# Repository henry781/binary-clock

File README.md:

# Binary Clock

A wall clock that shows the time in pure binary on 17 LEDs. It keeps time
with a 32.768 kHz watch crystal, sets itself from the DCF77 radio time
signal and dims its LEDs with the light of the room. Through-hole parts
(the DCF77 receiver module aside), on a round 180 mm board that is the
face of the clock.

> **Disclaimer:** this is a personal study project, shared as is in the
> hope that it is useful. It comes with no warranty and no support; build
> and use it at your own risk.

## Features

- **Display**: 17 LEDs, 10 mm: 5 red for the hours, 6 green for the
  minutes, 6 blue for the seconds. The time is held by three CD4040
  counters and shown through three 74HC245 buffers, with no multiplexing.
- **Timekeeping**: ATmega328P, Timer2 in asynchronous mode on a
  32.768 kHz crystal, CPU on its internal 8 MHz oscillator.
- **DCF77 synchronization**: a noise-tolerant software decoder that
  integrates the time over several minutes and follows DST changes and
  leap seconds. It never loaded a wrong time in 6,000 hours of simulated
  noisy signals; the rare corner cases are described in the
  [decoder documentation](docs/dcf77-decoder.md#validation).
- **Automatic dimming**: TEPT5700 light sensor, 488 Hz PWM in 2048 steps,
  from 0.1 % in the dark to full brightness in daylight.
- **Setting by hand**: three buttons, hours +1, minutes +1, seconds to 0.
- **Power**: 5 V from a cable coming out of the wall, on a screw terminal,
  with reverse-polarity protection; about 25 mA in a lit room.
- **Tested**: the decoder runs in a PC simulator against synthetic noise
  and a noise model fitted to recordings of the real receiver; CI builds
  the firmware and runs the regression suite.

Hardware revision B has been built and tested with this firmware.

## Reading the clock

Each row is a binary number, with weights increasing from left to right
as printed on the board. For 14:37:05:

```
             1  2  4  8  16 32
HOURS        ○  ●  ●  ●  ○          2 + 4 + 8  = 14
MINUTES      ●  ○  ●  ○  ○  ●       1 + 4 + 32 = 37
SECONDS      ●  ○  ●  ○  ○  ○       1 + 4      =  5
```

## How it works

```mermaid
flowchart LR
    XTAL["32.768 kHz crystal"] --> MCU["ATmega328P"]
    DCF["DCF77 receiver"] --> MCU
    LDR["Light sensor"] --> MCU
    BTN["3 buttons"] --> MCU
    MCU -- "clock and reset pulses" --> CNT["3 × CD4040 counters"]
    CNT --> BUF["3 × 74HC245 buffers"]
    MCU -- "dimming PWM on output enable" --> BUF
    BUF --> LED["17 LEDs"]
```

Every second, Timer2 wakes the microcontroller, which sends a clock pulse
to the seconds counter and carries into the minutes and hours counters.
The counter outputs drive the LEDs through the buffers; the
microcontroller dims them all at once by switching the buffers' output
enable at 488 Hz with a duty cycle that follows the room light. When a
DCF77 time is confirmed, the firmware reloads the counters and re-aligns
the phase of its seconds on the top of the minute.

## The board

| 3D render, front | PCB layout (front and back copper) |
|:---:|:---:|
|  |  |

Rendered from the KiCad project with `kicad-cli pcb render` and
`kicad-cli pcb export svg`. The 3D model shows every LED in red; on the
real clock the minutes are green and the seconds blue.

## Repository layout

| Path | Content |
|------|---------|
| [`hardware/`](hardware) | KiCad 10 project (schematic, PCB, project libraries) and bill of materials |
| [`firmware/binary_clock/`](firmware/binary_clock) | clock firmware, an Arduino sketch for MiniCore |
| [`firmware/test/`](firmware/test) | PC simulator and regression tests of the DCF77 decoder |
| [`firmware/tools/`](firmware/tools) | bring-up sketches and a crystal drift logger |
| [`docs/`](docs) | documentation |

## Documentation

- [Hardware](docs/hardware.md): circuit description, pinout, PCB.
- [Firmware](docs/firmware.md): building, programming, build options, architecture, debug output.
- [DCF77 decoder](docs/dcf77-decoder.md): how the time is recovered from a noisy signal, and how well.
- [Building the clock](docs/assembly.md): ordering the PCB, assembly, bring-up, mounting, troubleshooting.

## Quick start

1. Order the PCB ([ordering](docs/assembly.md#ordering-the-pcb)) and the
   parts listed in [`hardware/bom.csv`](hardware/bom.csv).
2. Assemble and check the board step by step: [assembly.md](docs/assembly.md).
3. Program the ATmega328P through the ISP header with an Arduino Uno as
   programmer: [firmware.md](docs/firmware.md#building-and-programming).
   With avr-gcc and avrdude:

   ```sh
   make -C firmware
   make -C firmware fuses flash PORT=/dev/ttyACM0
   ```

4. Run the decoder tests on a PC:

   ```sh
   make -C firmware/test test
   ```

## License

[MIT](LICENSE), hardware and software. `firmware/tools/arduino_isp_clock` is
derived from the ArduinoISP example, © 2008–2011 Randall Bohn, BSD license
(see the notice in the file).

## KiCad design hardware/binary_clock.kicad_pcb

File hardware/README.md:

# Hardware

KiCad 10 project of the clock, board revision B.

| File | Content |
|------|---------|
| `binary_clock.kicad_pro` | project file, open this one |
| `binary_clock.kicad_sch` | schematic |
| `binary_clock.kicad_pcb` | PCB |
| `binary_clock.kicad_sym`, `binary_clock.pretty/` | project libraries: symbol and footprint of the DCF77 module |
| `sym-lib-table`, `fp-lib-table` | project library tables |
| [`bom.csv`](bom.csv) | bill of materials |

Round board, Ø 180 mm, two layers. All parts go on the front; they are
through-hole parts, except the DCF77 module. The circuit is described in
[docs/hardware.md](../docs/hardware.md); fabrication files and assembly
are covered in [docs/assembly.md](../docs/assembly.md).

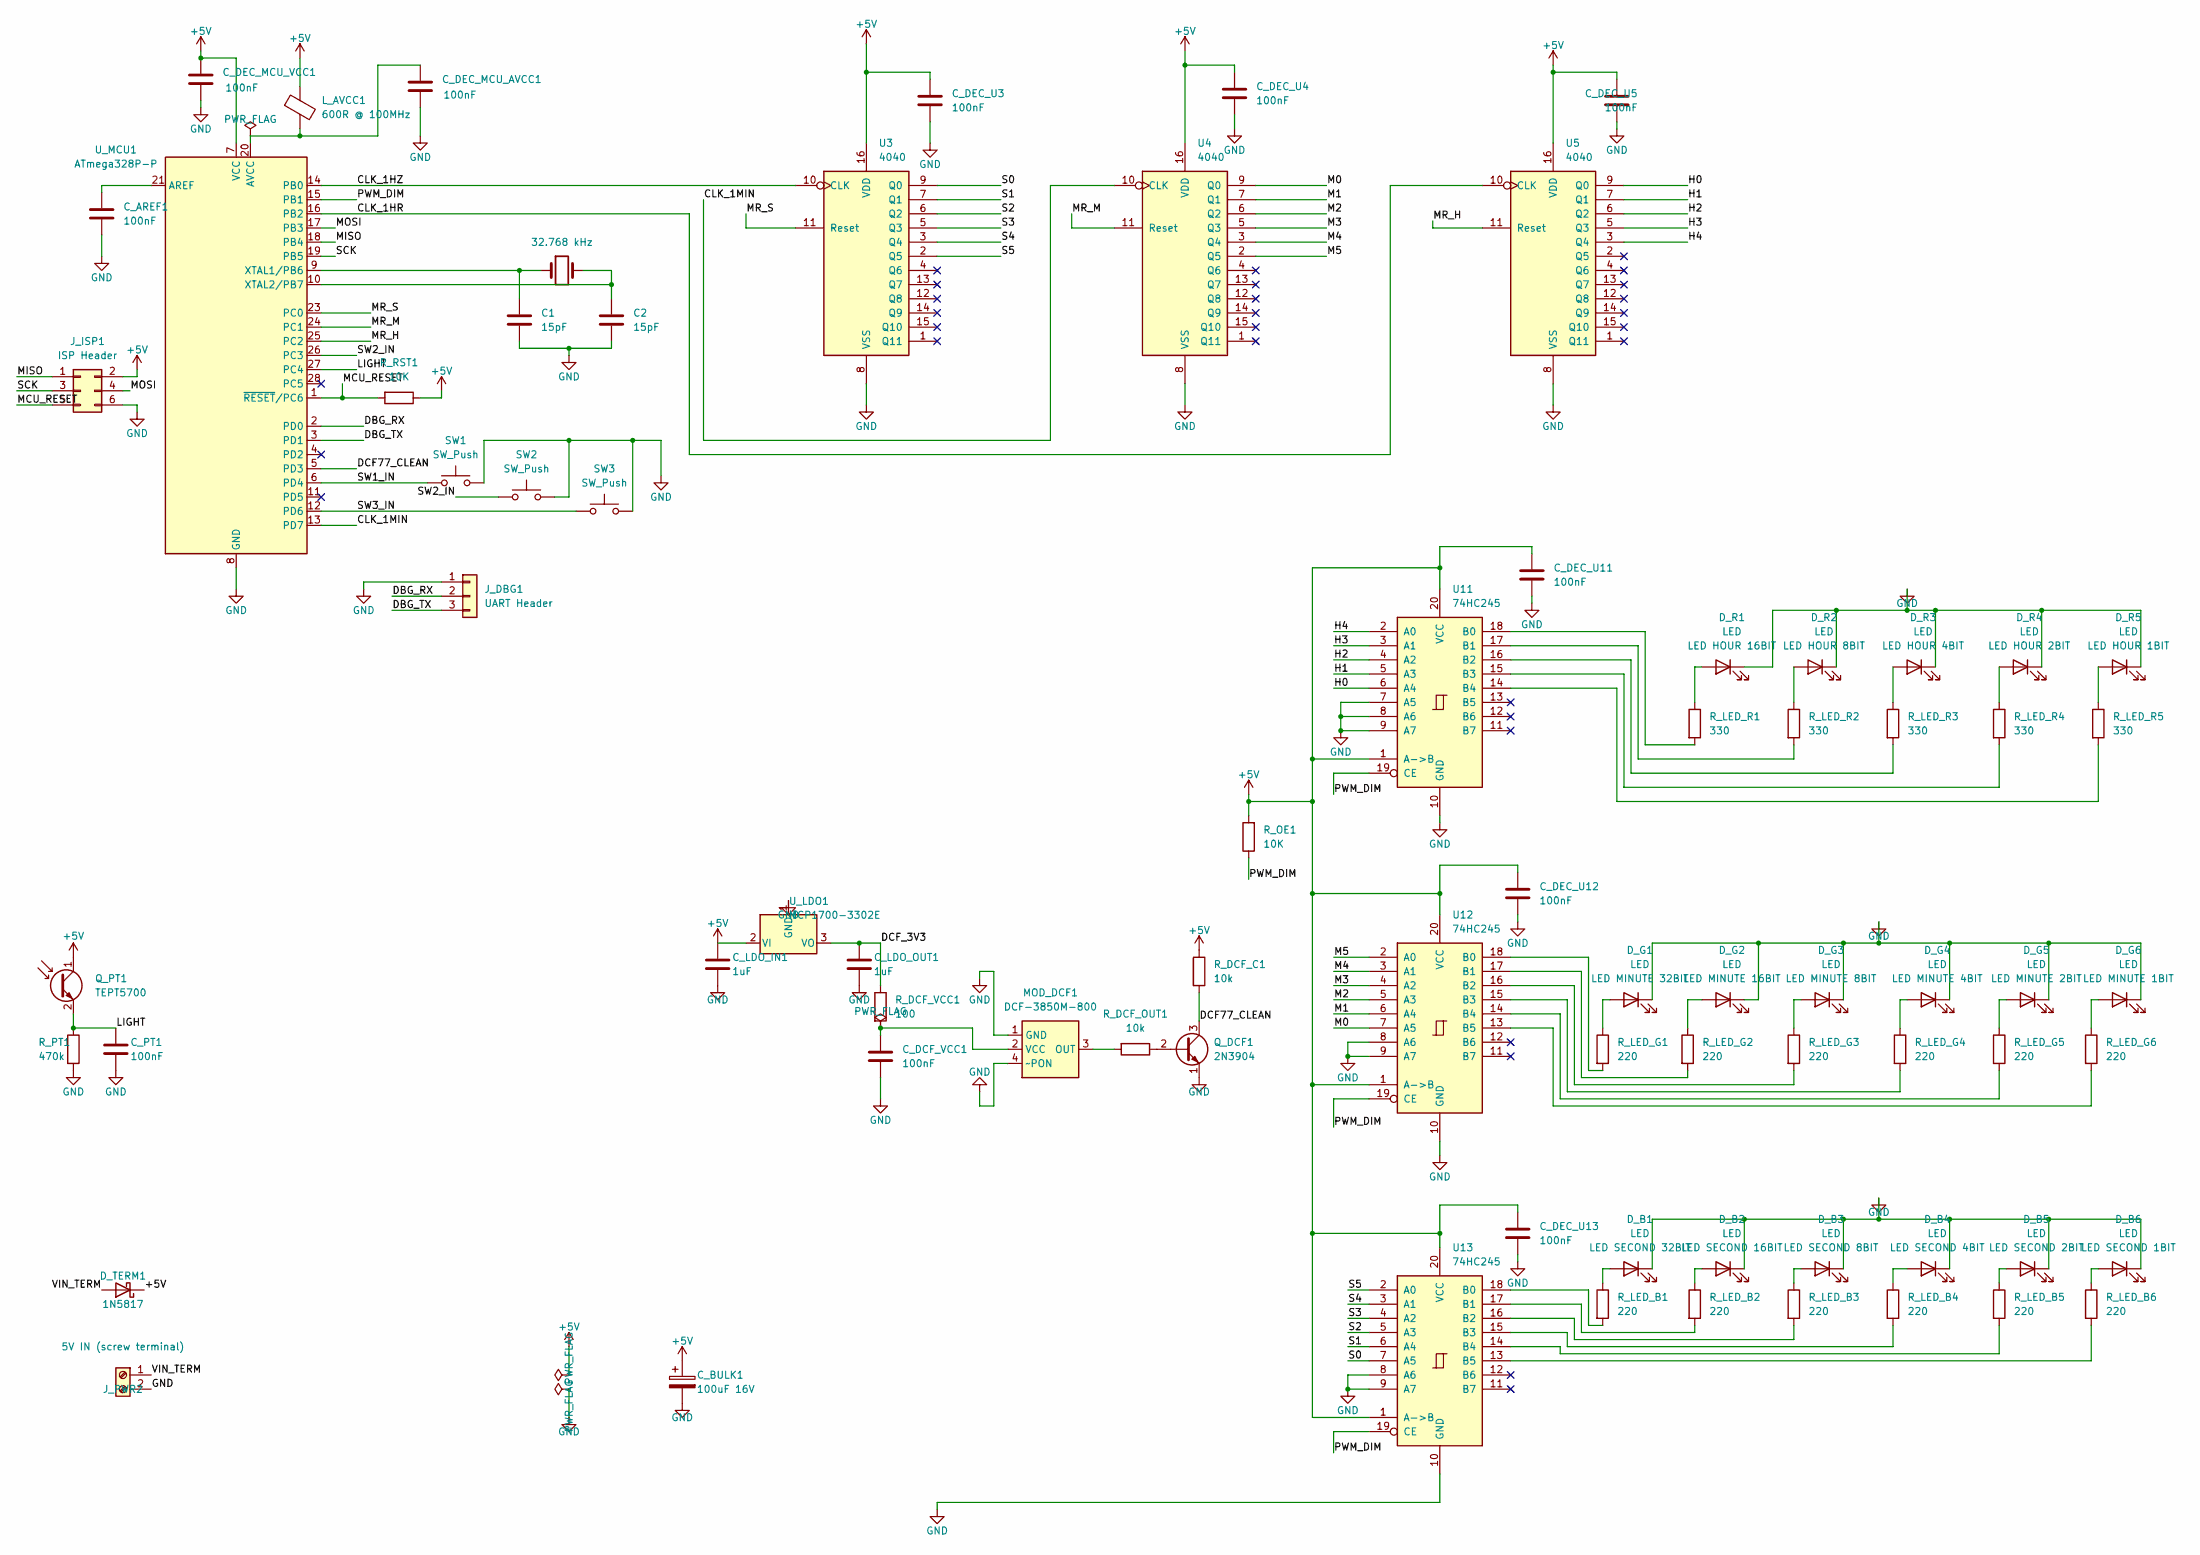
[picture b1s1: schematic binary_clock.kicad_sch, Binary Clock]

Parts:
C1, C2: 15pF; C_Disc_D5.0mm_W2.5mm_P5.00mm
C_AREF1: 100nF; C_Disc_D5.0mm_W2.5mm_P5.00mm
C_BULK1: 100uF 16V; CP_Radial_D6.3mm_P2.50mm
C_DCF_VCC1: 100nF; C_Disc_D5.0mm_W2.5mm_P5.00mm
C_DEC_MCU_AVCC1: 100nF; C_Disc_D5.0mm_W2.5mm_P5.00mm
C_DEC_MCU_VCC1: 100nF; C_Disc_D5.0mm_W2.5mm_P5.00mm
C_DEC_U3, C_DEC_U4, C_DEC_U5, C_DEC_U11, C_DEC_U12, C_DEC_U13: 100nF; C_Disc_D5.0mm_W2.5mm_P5.00mm
C_LDO_IN1: 1uF; C_Disc_D5.0mm_W2.5mm_P5.00mm
C_LDO_OUT1: 1uF; C_Disc_D5.0mm_W2.5mm_P5.00mm
C_PT1: 100nF; C_Disc_D5.0mm_W2.5mm_P5.00mm
D_B1, D_B2, D_B3, D_B4, D_B5, D_B6: LED; LED_D10.0mm
D_G1, D_G2, D_G3, D_G4, D_G5, D_G6: LED; LED_D10.0mm
D_R1, D_R2, D_R3, D_R4, D_R5: LED; LED_D10.0mm
D_TERM1: 1N5817; D_DO-41_SOD81_P10.16mm_Horizontal
J_DBG1: UART Header; PinHeader_1x03_P2.54mm_Vertical
J_ISP1: ISP Header; PinHeader_2x03_P2.54mm_Vertical
J_PWR2: 5V IN (screw terminal); TerminalBlock_Phoenix_MKDS-1,5-2_1x02_P5.00mm_Horizontal
L_AVCC1: 600R @ 100MHz; L_Axial_L9.5mm_D4.0mm_P12.70mm_Horizontal_Fastron_SMCC
MOD_DCF1: DCF-3850M-800; DCF77_Module_RC8000_Castellated_21.5x13mm
Q_DCF1: 2N3904; TO-92_Inline_Wide
Q_PT1: TEPT5700; LED_D5.0mm
R_DCF_C1: 10k; R_Axial_DIN0207_L6.3mm_D2.5mm_P10.16mm_Horizontal
R_DCF_OUT1: 10k; R_Axial_DIN0207_L6.3mm_D2.5mm_P10.16mm_Horizontal
R_DCF_VCC1: 100; R_Axial_DIN0207_L6.3mm_D2.5mm_P10.16mm_Horizontal
R_LED_B1, R_LED_B2, R_LED_B3, R_LED_B4, R_LED_B5, R_LED_B6: 220; R_Axial_DIN0207_L6.3mm_D2.5mm_P10.16mm_Horizontal
R_LED_G1, R_LED_G2, R_LED_G3, R_LED_G4, R_LED_G5, R_LED_G6: 220; R_Axial_DIN0207_L6.3mm_D2.5mm_P10.16mm_Horizontal
R_LED_R1, R_LED_R2, R_LED_R3, R_LED_R4, R_LED_R5: 330; R_Axial_DIN0207_L6.3mm_D2.5mm_P10.16mm_Horizontal
R_OE1: 10K; R_Axial_DIN0207_L6.3mm_D2.5mm_P10.16mm_Horizontal
R_PT1: 470k; R_Axial_DIN0207_L6.3mm_D2.5mm_P10.16mm_Horizontal
R_RST1: 10K; R_Axial_DIN0207_L6.3mm_D2.5mm_P10.16mm_Horizontal
SW1, SW2, SW3: SW_Push; SW_PUSH_6mm
U3, U4, U5: 4040; DIP-16_W7.62mm
U11, U12, U13: 74HC245; DIP-20_W7.62mm
U_LDO1: MCP1700-3302E; TO-92_Inline_Wide
U_MCU1: ATmega328P-P; DIP-28_W7.62mm
Y1: 32.768 kHz; Crystal_C38-LF_D3.0mm_L8.0mm_Horizontal

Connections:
+5V: C_BULK1.1, C_DEC_MCU_VCC1.1, C_DEC_U3.1, C_DEC_U4.1, C_DEC_U5.1, C_DEC_U11.1, C_DEC_U12.1, C_DEC_U13.1, C_LDO_IN1.1, D_TERM1.1 (K), J_ISP1.2, L_AVCC1.1, Q_PT1.1 (C), R_DCF_C1.1, R_OE1.2, R_RST1.1, U3.16 (VDD), U4.16 (VDD), U5.16 (VDD), U11.1 (A->B), U11.20 (VCC), U12.1 (A->B), U12.20 (VCC), U13.1 (A->B), U13.20 (VCC), U_LDO1.2 (VI), U_MCU1.7 (VCC)
/CLK_1HR: U5.10 (CLK), U_MCU1.16 (PB2)
/CLK_1HZ: U3.10 (CLK), U_MCU1.14 (PB0)
/CLK_1MIN: U4.10 (CLK), U_MCU1.13 (PD7)
/DBG_RX: J_DBG1.2, U_MCU1.2 (PD0)
/DBG_TX: J_DBG1.3, U_MCU1.3 (PD1)
/DCF77_CLEAN: Q_DCF1.3 (C), R_DCF_C1.2, U_MCU1.5 (PD3)
/DCF_3V3: C_LDO_OUT1.1, R_DCF_VCC1.1, U_LDO1.3 (VO)
/H0: U5.9 (Q0), U11.6 (A4)
/H1: U5.7 (Q1), U11.5 (A3)
/H2: U5.6 (Q2), U11.4 (A2)
/H3: U5.5 (Q3), U11.3 (A1)
/H4: U5.3 (Q4), U11.2 (A0)
/LIGHT: C_PT1.1, Q_PT1.2 (E), R_PT1.1, U_MCU1.27 (PC4)
/M0: U4.9 (Q0), U12.7 (A5)
/M1: U4.7 (Q1), U12.6 (A4)
/M2: U4.6 (Q2), U12.5 (A3)
/M3: U4.5 (Q3), U12.4 (A2)
/M4: U4.3 (Q4), U12.3 (A1)
/M5: U4.2 (Q5), U12.2 (A0)
/MCU_RESET: J_ISP1.5, R_RST1.2, U_MCU1.1 (~RESET/PC6)
/MISO: J_ISP1.1, U_MCU1.18 (PB4)
/MOSI: J_ISP1.4, U_MCU1.17 (PB3)
/MR_H: U5.11 (Reset), U_MCU1.25 (PC2)
/MR_M: U4.11 (Reset), U_MCU1.24 (PC1)
/MR_S: U3.11 (Reset), U_MCU1.23 (PC0)
/PWM_DIM: R_OE1.1, U11.19 (CE), U12.19 (CE), U13.19 (CE), U_MCU1.15 (PB1)
/S0: U3.9 (Q0), U13.7 (A5)
/S1: U3.7 (Q1), U13.6 (A4)
/S2: U3.6 (Q2), U13.5 (A3)
/S3: U3.5 (Q3), U13.4 (A2)
/S4: U3.3 (Q4), U13.3 (A1)
/S5: U3.2 (Q5), U13.2 (A0)
/SCK: J_ISP1.3, U_MCU1.19 (PB5)
/SW1_IN: SW1.1, U_MCU1.6 (PD4)
/SW2_IN: SW2.1, U_MCU1.26 (PC3)
/SW3_IN: SW3.1, U_MCU1.12 (PD6)
/VIN_TERM: D_TERM1.2 (A), J_PWR2.1
GND: C1.2, C2.2, C_AREF1.2, C_BULK1.2, C_DCF_VCC1.2, C_DEC_MCU_AVCC1.2, C_DEC_MCU_VCC1.2, C_DEC_U3.2, C_DEC_U4.2, C_DEC_U5.2, C_DEC_U11.2, C_DEC_U12.2, C_DEC_U13.2, C_LDO_IN1.2, C_LDO_OUT1.2, C_PT1.2, D_B1.1 (K), D_B2.1 (K), D_B3.1 (K), D_B4.1 (K), D_B5.1 (K), D_B6.1 (K), D_G1.1 (K), D_G2.1 (K), D_G3.1 (K), D_G4.1 (K), D_G5.1 (K), D_G6.1 (K), D_R1.1 (K), D_R2.1 (K), D_R3.1 (K), D_R4.1 (K), D_R5.1 (K), J_DBG1.1, J_ISP1.6, J_PWR2.2, MOD_DCF1.1 (GND), MOD_DCF1.4 (~PON), Q_DCF1.1 (E), R_PT1.2, SW1.2, SW2.2, SW3.2, U3.8 (VSS), U4.8 (VSS), U5.8 (VSS), U11.7 (A5), U11.8 (A6), U11.9 (A7), U11.10 (GND), U12.8 (A6), U12.9 (A7), U12.10 (GND), U13.8 (A6), U13.9 (A7), U13.10 (GND), U_LDO1.1 (GND), U_MCU1.8 (GND), U_MCU1.22 (GND)
unnamed: D_B1.2 (A), R_LED_B1.1
unnamed: D_B2.2 (A), R_LED_B2.1
unnamed: D_B3.2 (A), R_LED_B3.1
unnamed: D_B4.2 (A), R_LED_B4.1
unnamed: D_B5.2 (A), R_LED_B5.1
unnamed: D_B6.2 (A), R_LED_B6.1
unnamed: D_G1.2 (A), R_LED_G1.1
unnamed: D_G2.2 (A), R_LED_G2.1
unnamed: D_G3.2 (A), R_LED_G3.1
unnamed: D_G4.2 (A), R_LED_G4.1
unnamed: D_G5.2 (A), R_LED_G5.1
unnamed: D_G6.2 (A), R_LED_G6.1
unnamed: D_R1.2 (A), R_LED_R1.1
unnamed: D_R2.2 (A), R_LED_R2.1
unnamed: D_R3.2 (A), R_LED_R3.1
unnamed: D_R4.2 (A), R_LED_R4.1
unnamed: D_R5.2 (A), R_LED_R5.1
unnamed: MOD_DCF1.3 (OUT), R_DCF_OUT1.2
unnamed: C_DCF_VCC1.1, MOD_DCF1.2 (VCC), R_DCF_VCC1.2
unnamed: Q_DCF1.2 (B), R_DCF_OUT1.1
unnamed: R_LED_R1.2, U11.18 (B0)
unnamed: R_LED_R2.2, U11.17 (B1)
unnamed: R_LED_R3.2, U11.16 (B2)
unnamed: R_LED_R4.2, U11.15 (B3)
unnamed: R_LED_R5.2, U11.14 (B4)
unnamed: R_LED_G1.2, U12.18 (B0)
unnamed: R_LED_G2.2, U12.17 (B1)
unnamed: R_LED_G3.2, U12.16 (B2)
unnamed: R_LED_G4.2, U12.15 (B3)
unnamed: R_LED_G5.2, U12.14 (B4)
unnamed: R_LED_G6.2, U12.13 (B5)
unnamed: R_LED_B1.2, U13.18 (B0)
unnamed: R_LED_B2.2, U13.17 (B1)
unnamed: R_LED_B3.2, U13.16 (B2)
unnamed: R_LED_B4.2, U13.15 (B3)
unnamed: R_LED_B5.2, U13.14 (B4)
unnamed: R_LED_B6.2, U13.13 (B5)
unnamed: C_AREF1.1, U_MCU1.21 (AREF)
unnamed: C_DEC_MCU_AVCC1.1, L_AVCC1.2, U_MCU1.20 (AVCC)
unnamed: C1.1, U_MCU1.9 (XTAL1/PB6), Y1.1
unnamed: C2.1, U_MCU1.10 (XTAL2/PB7), Y1.2

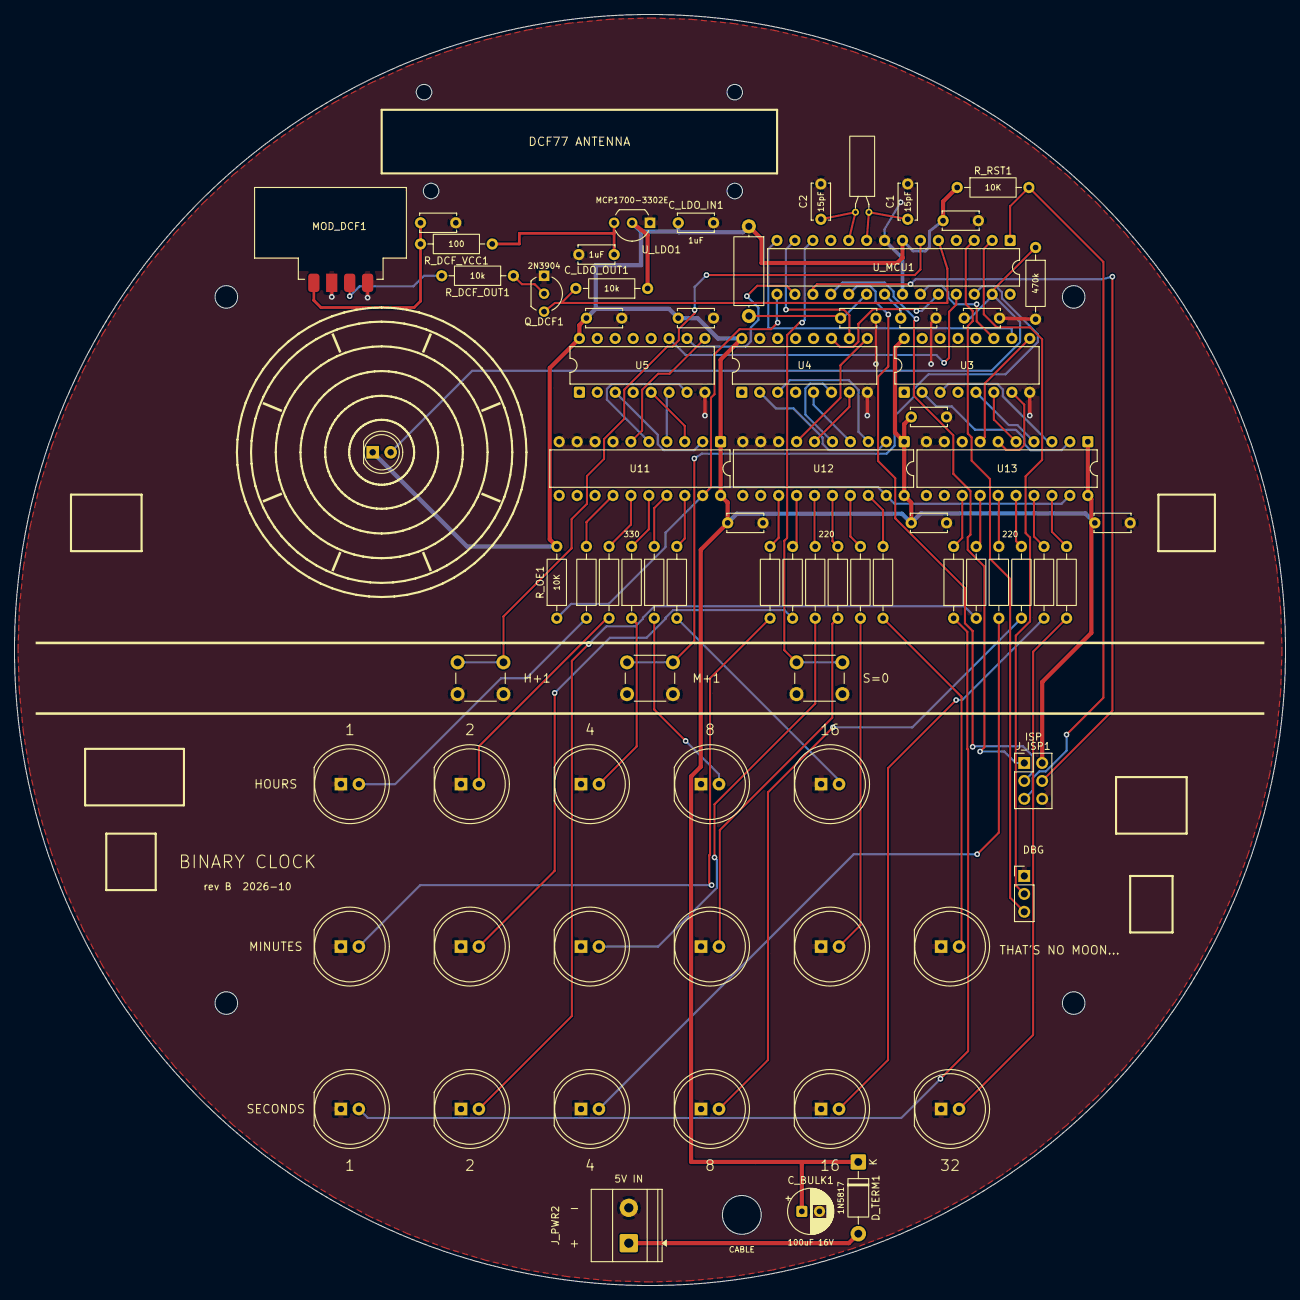
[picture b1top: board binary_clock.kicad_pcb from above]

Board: 2 copper layers, 180.0 x 180.0 mm, 85 parts (0 on the bottom side), 80 nets.

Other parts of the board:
H_CABLE1: cable 5V; MountingHole_5.5mm
MH1, MH2, MH3, MH4: MountingHole_3.2mm; MountingHole_3.2mm_M3
MH5, MH6, MH7, MH8: MountingHole_2.2mm; MountingHole_2.2mm_M2

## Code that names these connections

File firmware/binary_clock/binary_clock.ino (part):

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 *   1. 1 Hz timebase: Timer2 in asynchronous mode on the 32.768 kHz crystal,
 *      driving the CLK and MR inputs of the three CD4040 display counters;
 *   2. dimming: ambient light measured once per second on ADC4 (TEPT5700 +
 *      R_PT1), 488 Hz hardware PWM on PB1/OC1A driving ~OE of the 74HC245
 *      LED buffers;
 *   3. DCF77 decoding on INT1 (dcf77_decoder.h, docs/dcf77-decoder.md);
 *   4. three buttons, debounced by deferred sampling.
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#define DCF77_ENABLED        1  // DCF77 synchronization
#endif
#ifndef DCF77_OUT_ACTIVE_LOW
#define DCF77_OUT_ACTIVE_LOW 1  // 1: PD3 idles HIGH and pulses LOW. The receiver outputs HIGH
                                //    pulses at 3.3 V; the Q_DCF1 inverter turns them into
                                //    0/5 V LOW pulses on PD3.
                                // 0: receiver output wired straight to PD3, no inverter
#endif
#ifndef DCF77_PD3_PULLUP
#define DCF77_PD3_PULLUP     0  // 1 only for an open-collector receiver powered from 5 V
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#define DCF77_DEBUG_PULSES   0  // 1: print each decoded DCF77 second (docs/dcf77-decoder.md)
#endif
#ifndef DEBUG_UART_ENABLED
#define DEBUG_UART_ENABLED   1  // bit-banged TX on PD1, 9600 baud
#endif
#ifndef VERBOSE_TICK
#define VERBOSE_TICK         0  // 1: print "T <n> hh:mm:ss L <adc> <level>" every second
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// 2048, during which the LEDs are enabled (duty cycle = level / 2048).
#define PWM_TOP              2047 // Timer1 mode 14 (TOP = ICR1), /8: 8 MHz / 8 / 2048 = 488 Hz
#ifndef BRIGHT_CURVE
#define BRIGHT_CURVE         1    // 1: level proportional to light (constant contrast with
                                  //    the room); 2: quadratic, darker at dusk;
                                  // 0: square root, brighter at dusk
#endif
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// Pin mapping (docs/hardware.md)
// ---------------------------------------------------------------------
// Port B
#define PIN_CLK_1HZ   PB0  // 14 -> U3 CLK (seconds counter)
#define PIN_PWM       PB1  // 15 OC1A -> PWM_DIM: ~OE of the 74HC245 buffers
#define PIN_CLK_1HR   PB2  // 16 -> U5 CLK (hours counter)
// PB3/4/5 MOSI/MISO/SCK: ISP only, inputs with pull-up while running
// PB6/7 TOSC1/TOSC2: crystal Y1, owned by asynchronous Timer2

// Port C
#define PIN_MR_S      PC0  // 23 -> U3 MR
#define PIN_MR_M      PC1  // 24 -> U4 MR
#define PIN_MR_H      PC2  // 25 -> U5 MR
#define PIN_SW2       PC3  // 26 button minutes +1 (internal pull-up, PCINT11)
#define PIN_LIGHT     PC4  // 27 ADC4 <- TEPT5700 / R_PT1 (LIGHT)
// PC5: unused, output LOW
#define ADC_CH_LIGHT  4

// Port D
#define PIN_DBG_RX    PD0  //  2 debug RX (unused: input with pull-up)
#define PIN_DBG_TX    PD1  //  3 debug TX (bit-banged, 9600 baud)
// PD2: unused, output LOW
#define PIN_DCF_IN    PD3  //  5 INT1 <- DCF77_CLEAN
#define PIN_SW1       PD4  //  6 button hours +1 (internal pull-up, PCINT20)
// PD5: unused, output LOW. Next to TOSC2 (pin 10): nothing may switch here.
#define PIN_SW3       PD6  // 12 button seconds reset (internal pull-up, PCINT22)
#define PIN_CLK_1MIN  PD7  // 13 -> U4 CLK (minutes counter)

// ---------------------------------------------------------------------
// Direct port access
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// ---------------------------------------------------------------------
// CLK: idle HIGH -> falling edge (counts) -> 5 us LOW -> back HIGH.
//      The CD4040 counts on the falling edge; t_w >= 250 ns, 20x margin.
static inline void pulse_clk_s(void) { CLR_B(PIN_CLK_1HZ);  _delay_us(5); SET_B(PIN_CLK_1HZ);  }
static inline void pulse_clk_m(void) { CLR_D(PIN_CLK_1MIN); _delay_us(5); SET_D(PIN_CLK_1MIN); }
static inline void pulse_clk_h(void) { CLR_B(PIN_CLK_1HR);  _delay_us(5); SET_B(PIN_CLK_1HR);  }

// MR: idle LOW -> 10 us HIGH -> LOW. The CD4040 reset is active HIGH.
static inline void pulse_mr_s(void)  { SET_C(PIN_MR_S); _delay_us(10); CLR_C(PIN_MR_S); }
static inline void pulse_mr_m(void)  { SET_C(PIN_MR_M); _delay_us(10); CLR_C(PIN_MR_M); }
static inline void pulse_mr_h(void)  { SET_C(PIN_MR_H); _delay_us(10); CLR_C(PIN_MR_H); }

// Load a CD4040 with the value N: MR, then N CLK pulses (about 330 us for
// N = 59). The counter has no parallel load input.
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#if DEBUG_UART_ENABLED
// One bit lasts 104.2 us at 9600 baud; DBG_BIT_US also absorbs the loop
// overhead (about 1 us). The internal RC oscillator is factory-calibrated
// to +/-10 % only: measure one bit on PD1 and scale this value if the
// terminal shows garbage (a chip running 9 % fast needs 112).
#ifndef DBG_BIT_US
#define DBG_BIT_US 103
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static void dbg_putc(char c)
{
  // Start bit (LOW)
  CLR_D(PIN_DBG_TX); _delay_us(DBG_BIT_US);
  // 8 data bits, LSB first
  for (uint8_t i = 0; i < 8; i++) {
    if (c & 1) SET_D(PIN_DBG_TX); else CLR_D(PIN_DBG_TX);
    _delay_us(DBG_BIT_US);
    c >>= 1;
  }
  // Stop bit (HIGH)
  SET_D(PIN_DBG_TX); _delay_us(DBG_BIT_US);
}

static void dbg_puts(const char *s) { while (*s) dbg_putc(*s++); }
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static void init_gpio(void)
{
  // Port B: CLK lines are outputs idling HIGH (the CD4040 counts on the
  // falling edge); PB1 (PWM) is an output driven HIGH until Timer1 takes
  // over (~OE HIGH = LEDs off during start-up).
  // PB3/4/5 (ISP): inputs with pull-up, never floating; the pull-ups do not
  // disturb the programmer.
  // PB6/7 (TOSC): owned by asynchronous Timer2, DDR/PORT left alone.
  DDRB  = _BV(PIN_CLK_1HZ) | _BV(PIN_PWM) | _BV(PIN_CLK_1HR);
  PORTB = _BV(PIN_CLK_1HZ) | _BV(PIN_PWM) | _BV(PIN_CLK_1HR)
        | _BV(PB3) | _BV(PB4) | _BV(PB5);

  // Port C: MR lines are outputs idling LOW; PC3 = SW2 input with pull-up;
  // PC4 = LIGHT analog input (no pull-up); PC5 unused, output LOW.
  DDRC  = _BV(PIN_MR_S) | _BV(PIN_MR_M) | _BV(PIN_MR_H) | _BV(PC5);
  PORTC = _BV(PIN_SW2);

  // Port D:
  //   PD0 RX       : input with pull-up (unused, must not float)
  //   PD1 TX       : output, idle HIGH (UART idle level)
  //   PD2          : unused, output LOW
  //   PD3 DCF_IN   : input, pull-up per DCF77_PD3_PULLUP
  //   PD4/PD6 SW*  : inputs, internal pull-up
  //   PD5          : unused, output LOW (next to TOSC2: never switches)
  //   PD7 CLK_1MIN : output, idle HIGH (the CD4040 counts on the falling edge)
  DDRD  = _BV(PIN_DBG_TX) | _BV(PIN_CLK_1MIN) | _BV(PD2) | _BV(PD5);
  PORTD = _BV(PIN_DBG_TX) | _BV(PIN_CLK_1MIN) | _BV(PIN_DBG_RX)
        | _BV(PIN_SW1) | _BV(PIN_SW3)
#if DCF77_PD3_PULLUP
        | _BV(PIN_DCF_IN)
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  MCUCR &= ~_BV(PUD);

  // Digital input buffers off on the analog input (ADC4) and on the unused
  // PC5. PC3 (SW2) stays digital.
  DIDR0 = _BV(ADC4D) | _BV(ADC5D);

  ACSR |= _BV(ACD);       // analog comparator off
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
  // Timer1: Fast PWM, TOP = ICR1 = 2047 (mode 14), prescaler /8
  //   f = 8 MHz / 8 / 2048 = 488 Hz, 2048 steps (0.05 % each).
  //   OC1A (PB1) non-inverting: HIGH from 0 to OCR1A, LOW after.
  //   ~OE is active LOW, so the LEDs are enabled during the LOW part, i.e.
  //   (PWM_TOP - OCR1A) steps out of 2048. OCR1A = PWM_TOP keeps the output
  //   HIGH: LEDs off. No ISR touches Timer1, so the 16-bit writes from
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static void init_interrupts(void)
{
#if DCF77_ENABLED
  // INT1 on any logical change of PD3 (DCF77_CLEAN). Edge detection needs
  // the I/O clock, hence IDLE sleep only.
  EICRA = (EICRA & ~(_BV(ISC11) | _BV(ISC10))) | _BV(ISC10);
  EIFR  = _BV(INTF1);
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  EIMSK = 0;
#endif

  // Buttons: PD4 (SW1) = PCINT20, PD6 (SW3) = PCINT22 -> PCINT2_vect;
  //          PC3 (SW2) = PCINT11 -> PCINT1_vect
  PCMSK2 = _BV(PCINT20) | _BV(PCINT22);
  PCMSK1 = _BV(PCINT11);
  PCIFR  = _BV(PCIF2) | _BV(PCIF1);
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  TIFR2  = _BV(OCF2A);
  TIMSK2 |= _BV(OCIE2A);
}
ISR(PCINT2_vect) { arm_button_sample(); }   // SW1 (PD4), SW3 (PD6)
ISR(PCINT1_vect) { arm_button_sample(); }   // SW2 (PC3)

// Timer2 compare A: 20 ms after the last edge, read the buttons again
ISR(TIMER2_COMPA_vect)
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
